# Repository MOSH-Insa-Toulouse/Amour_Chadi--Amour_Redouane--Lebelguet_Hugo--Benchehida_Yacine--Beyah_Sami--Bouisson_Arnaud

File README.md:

# Capteur de gaz connecté - UF SMART DEVICE - INSA Toulouse 

Introduction : Ce projet s'inscrit dans le cadre de notre formation d'ingénieur à l'INSA Toulouse en 5ème année sur les objets connectés. Plus précisément, l'objectif était de pouvoir comprendre toute l'architecture IoT associée à un système connecté, de sa fabrication à son implémentation sur un réseau sans fil basse consommation. A ce titre nous avons conçu un capteur de gaz connecté capable de détecter plusieurs substances telles que de l'ammoniac, de l'éthanol ou même de l'air synthétique. Pour ce faire, nous avons d'abord fabriqué le capteur à base de nanoparticules en salle blanche dans un laboratoire de nano-micro-fabrication (AIME) à l'INSA Toulouse. Afin de récupérer la mesure du capteur, nous avons aussi conçu le circuit électrique sur LT-Spice permettant d'acquérir le signal analogique. Ce circuit a ensuite été embarqué et intégré sur une carte électronique conçue sur le logiciel KiCad. Nous avons connecté la sortie de cette carte à un microcontrôleur Arduino et branché sur les ports UART (TX/RX) un module LoRa permettant de communiquer les valeurs du capteur sur le réseau TTN (The Things Network). Nous avons programmé le tout sur l'IDE Arduino et NodeRed afin d'afficher cette donnée sur un dashboard web et élaboré la fiche technique (datasheet) expliquant l'utilisation typique de ce capteur : 

**Apperçu du capteur de gaz à base de nanoparticules**

**Chronologie du projet**

**Organisation de l'équipe**

# *** 1. Micro-Nano-fabrication en salle blanche ***

Aujourd’hui les capteurs de gaz présentent un réel potentiel pour répondre aux problématiques environnementales. Pour rappel, l’objectif était de développer un capteur de gaz chimique à base de nanoparticules de trioxyde de tungstène (WO3), de l’intégrer dans un circuit électronique afin de mesurer la concentration de gaz et de la communiquer ensuite sur un Dashboard web en utilisant le protocole de communication LoRa.  Ce projet nous permet d’étudier et de déployer toute l’architecture IoT associée à un système connecté. Il nous a aussi permis de comprendre les enjeux liés aux objets connectés : le faible encombrement, la faible consommation énergétique et le faible coût. 

---> Ce capteur de gaz répond à la problématique de faible encombrement puisqu’il intègre quatre éléments de mesure sur seulement quelques millimètres (voir figure- ci-dessous) : 
-	Deux capteurs en aluminium symétriques, sous forme de peignes interdigités séparés de 5 µm. Ces peignes permettent de piéger et d’intégrer des nanoparticules WO3, constituant des chemins de conduction électriques parallèles au sein des peignes et sensibles à certains gaz. Lorsqu’une réaction d’oxydoréduction a lieu entre les nanoparticules et un gaz d’intérêt, la résistance électrique au sein des peignes est modifiée. Cette variation de résistance électrique est liée à la concentration de gaz. 
-	Une résistance chauffante de poly silicium enfouie et isolée électriquement par une couche de SiO₂. Elle permet de chauffer la puce et d’y réguler la température autour de 250°C, température optimale pour une meilleure sensibilité des capteurs d’aluminium.
-	Un résistance d’aluminium en serpentin pour mesurer la température à la surface.
-	Des électrodes pour la connexion aux appareils de mesure extérieurs. Pour mesurer cette résistance électrique, nous avons réalisé les contacts électriques par métallisation à l'aluminium. Plus précisément nous avons utilisé la technique de photogravure consistant à déposer une couche de résine photosensible sur l'aluminium, à insoler cette résine au niveau des zones d'aluminium que l'on souhaite retirer et à les attaquer chimiquement dans un bain acide.

Une fois les contacts faits, nous avons réalisé la synthèse chimique des nanoparticules WO3 pour ensuite les intégrer par diélectrophorèse au sein des peignes interdigités. Cette technique consiste à déposer une fine goutte de nanoparticules sur le capteur et à appliquer pendant 60s un champ électrique alternatif oscillant à la fréquence de 100 KHz avec une amplitude de 10V, entre les électrodes des peignes interdigités afin d’y attirer et d’y piéger les nanoparticules. 

---> Ce capteur répond aussi à la problématique de faible coût et de respect de l’environnement puisque la synthèse chimique des batônnets de nanoparticules n’implique que quelques millilitres de solution réutilisables chaque année afin d’éviter tout gaspillage. La quantité a même été diminuée de moitié cette année par rapport aux années précédentes. Les produits de la synthèse sont également triés afin de ne pas polluer les eaux usées. Voici une image au microscope optique de notre capteur après intégration des nanoparticules :

---> Enfin, ce capteur répond à la problématique de faible consommation puisque la résistance électrique de chaque peigne interdigité est théoriquement de l’ordre de la centaine de MΩ, ce qui correspond à une consommation en courant électrique de quelques micro-ampères voire nanoampères. 

# *** 2. CAO Electronique et réalisation du circuit ***

Une fois le capteur fabriqué, l'objectif était d'établir le circuit électronique suivant permettant de traduire la variation de résistance électrique du capteur (Isens), en tension analogique (ADC). Ce circuit inclut la puce fabriquée en AIME avec le boîtier TO5, un filtre RC passif passe-bas à l’entrée pour couper le bruit à hautes fréquences (50Hz) ainsi que le couplage capacitif avec le réseau à 230V, un amplificateur opérationnel Trans-impédance LTC1050 à deux étages, une résistance de Shunt, un filtre passe-bas actif en sortie de l’amplificateur et enfin un filtre passif anti-repliement en sortie du circuit côté ADC pour retirer le bruit introduit en cours de traitement.  

Nous avons dans un second temps conçu la carte électronique permettant d'intégrer l'ensemble du circuit. Nous avons pour cela utilisé le logiciel KiCad en deux étapes : 

1) Réalisation schématique du circuit visant simplement à positionner les symboles de chaque composant, à les connecter et à leur associer leur empreinte (footprint). Ce schéma électrique est constitué de trois parties : le circuit pour le capteur de gaz, l'arduino permettant de récupérer la valeur analogique côté ADC en sortie du circuit et le module RF de communication LoRa connecté aux pins digitaux de l'arduino : 

2) Réalisation du PCB visant à positionner les empreintes de chaque composant sur la carte non plus de manière symbolique mais de manière réelle. Y sont ainsi déssinés le routage des pistes de cuivre interconnectant les empreintes ainsi que les deux couches de cuivre (TOP et BOTTOM) et le plan de masse. Nous y avons appliqué les règles de conception de classe 2 en prenant en compte les moyens de fabrication de notre établissement (largeur des pistes et isolation minimum à 0.6 mm). Voici une image 2D et 3D de notre carte PCB simple face intégrant les composants électroniques traversants du côté TOP et les pistes du côté  BOTTOM avec quelques vias : 

PCB et Routage

TOP et BOTTOM VIEW

Voici la liste compléte des composants principaux avec leur symbole et leur empreinte, que nous avons utilisés pour ce circuit. (cf. fichier csv pour plus d'informations "bills of materials") :

- Capteur de gaz à nanoparticules

- un commutateur à glissière trois pattes afin de sélectionner au choix l'un des deux capteurs de gaz : 

- Un bornier à vis 2 pattes pour l'alimentation externe de 0 à 15V pour la résistance chauffante : 

- un amplificateur transimpédance : 

- Le module LoRa et son breakout board. Nous avons nous-mêmes édité le footprint en prenant soin d'y placer les pads à un pas de 2.54 mm et les trous de perçage permettant de fixer le module : 

# *** Datasheet ***

Dans l’industrie électronique, il est standard d’accompagner chaque composant d’une fiche technique fournissant les caractéristiques de fonctionnement standard, les résultats d’essais, les recommandations d’usage et d’autres renseignements. Vous trouverez dans le dépôt, la datasheet que l'on a réalisé.

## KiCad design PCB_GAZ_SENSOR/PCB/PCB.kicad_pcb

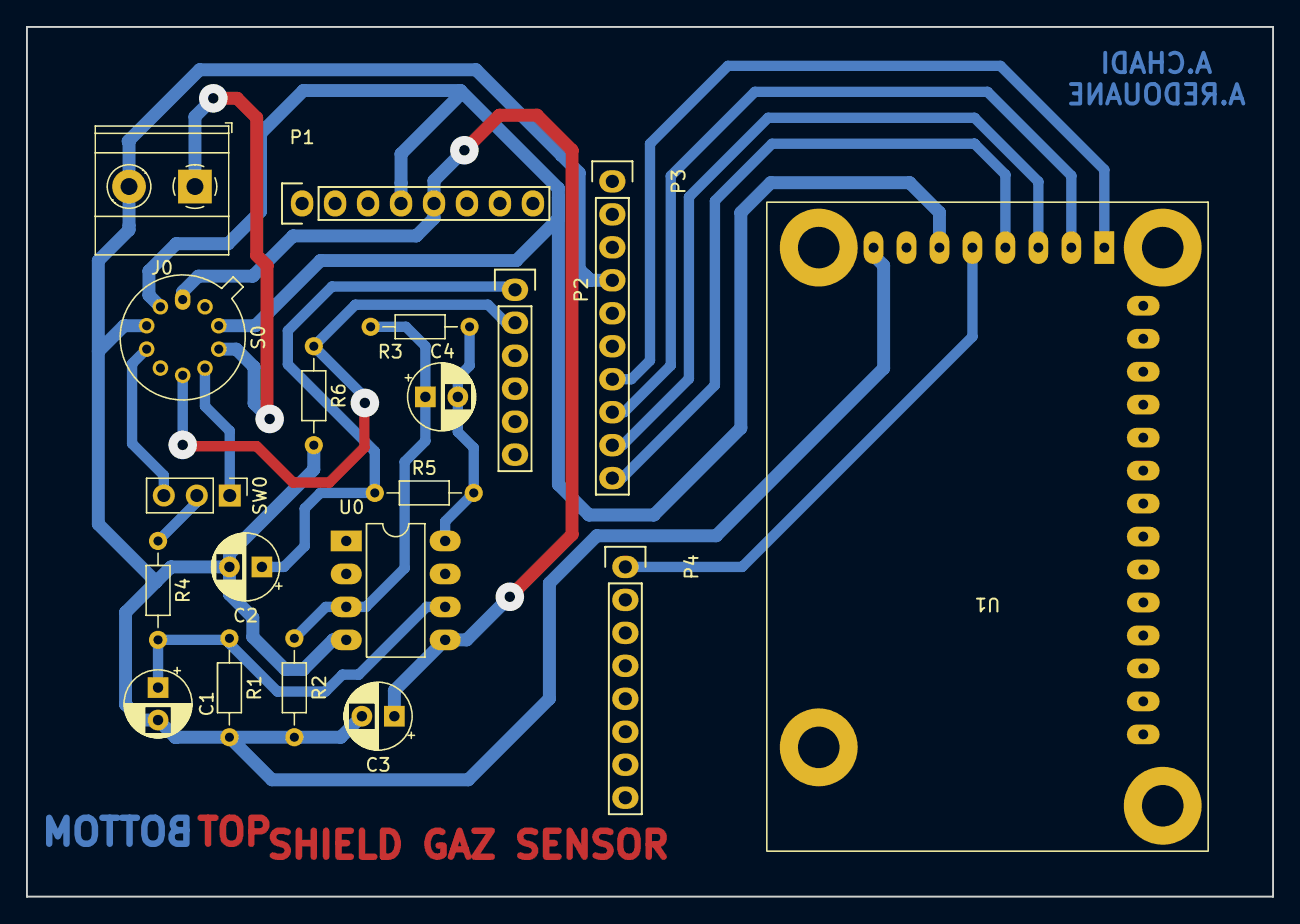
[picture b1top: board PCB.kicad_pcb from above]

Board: 2 copper layers, 96.0 x 67.0 mm, 19 parts (0 on the bottom side), 17 nets.

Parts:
C1, C2, C3: 100n; CP_Radial_D5.0mm_P2.50mm
C4: 1u; CP_Radial_D5.0mm_P2.50mm
J0: Screw_Terminal_01x02; TerminalBlock_Phoenix_MKDS-1,5-2-5.08_1x02_P5.08mm_Horizont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
P1: Power; Socket_Strip_Arduino_1x08
P2: Analog; Socket_Strip_Arduino_1x06
P3: Digital; Socket_Strip_Arduino_1x10
P4: Digital; Socket_Strip_Arduino_1x08
R1, R3: 100k; R_Axial_DIN0204_L3.6mm_D1.6mm_P7.62mm_Horizontal
R2: R_CAL; R_Axial_DIN0204_L3.6mm_D1.6mm_P7.62mm_Horizontal
R4: 10k; R_Axial_DIN0204_L3.6mm_D1.6mm_P7.62mm_Horizontal
R5: 1k; R_Axial_DIN0204_L3.6mm_D1.6mm_P7.62mm_Horizontal
R6: R_adjust; R_Axial_DIN0204_L3.6mm_D1.6mm_P7.62mm_Horizontal
S0: Sensor_Aime; TO-5-10_Window
SW0: SW_DPDT_x2; PinHeader_1x03_P2.54mm_Vertical
U0: LTC1050; DIP-8_W7.62mm_LongPads
U1: RN2483_Breakout; RN2483_FOOTPRINT

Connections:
+3V3: P1.4, S0.2 (GazSensorRight), S0.9 (GazSensorLeft), U1.6 (3V3)
+5V: C3.1, P1.5, S0.1 (TempSensor), U0.5 (V+)
+15V: J0.1, S0.8 (HeatResistor)
/7: P4.1, U1.5 (RST)
/8: P3.10, U1.4 (RTS)
/9(**): P3.9, U1.3 (CTS)
/10(**/SS): P3.8, U1.2 (RX_LoRa)
/11(**/MOSI): P3.7, U1.1 (TX_LoRa)
ADC_GAZ: C2.1, P2.1, R5.1
GND: C1.2, C2.2, C3.2, J0.2, P3.4, R1.2, R2.2, R6.2, S0.3 (HeatResistor), U0.4 (V-), U1.8 (GND)
unnamed: C4.2, R3.1, R5.2, U0.8
unnamed: S0.7 (GazSensorLeft), SW0.1 (A)
unnamed: S0.4 (GazSensorRight), SW0.3 (C)
unnamed: R4.1, SW0.2 (B)
unnamed: C1.1, R1.1, R4.2, U0.6 (+)
unnamed: C4.1, R2.1, R3.2, U0.3 (-)
TempADC: P2.2, R6.1, S0.6 (TempSensor)

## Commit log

2022-01-05 final version
2022-01-13 Datasheet
2022-02-05 Add arduino code
2022-02-05 last edition
